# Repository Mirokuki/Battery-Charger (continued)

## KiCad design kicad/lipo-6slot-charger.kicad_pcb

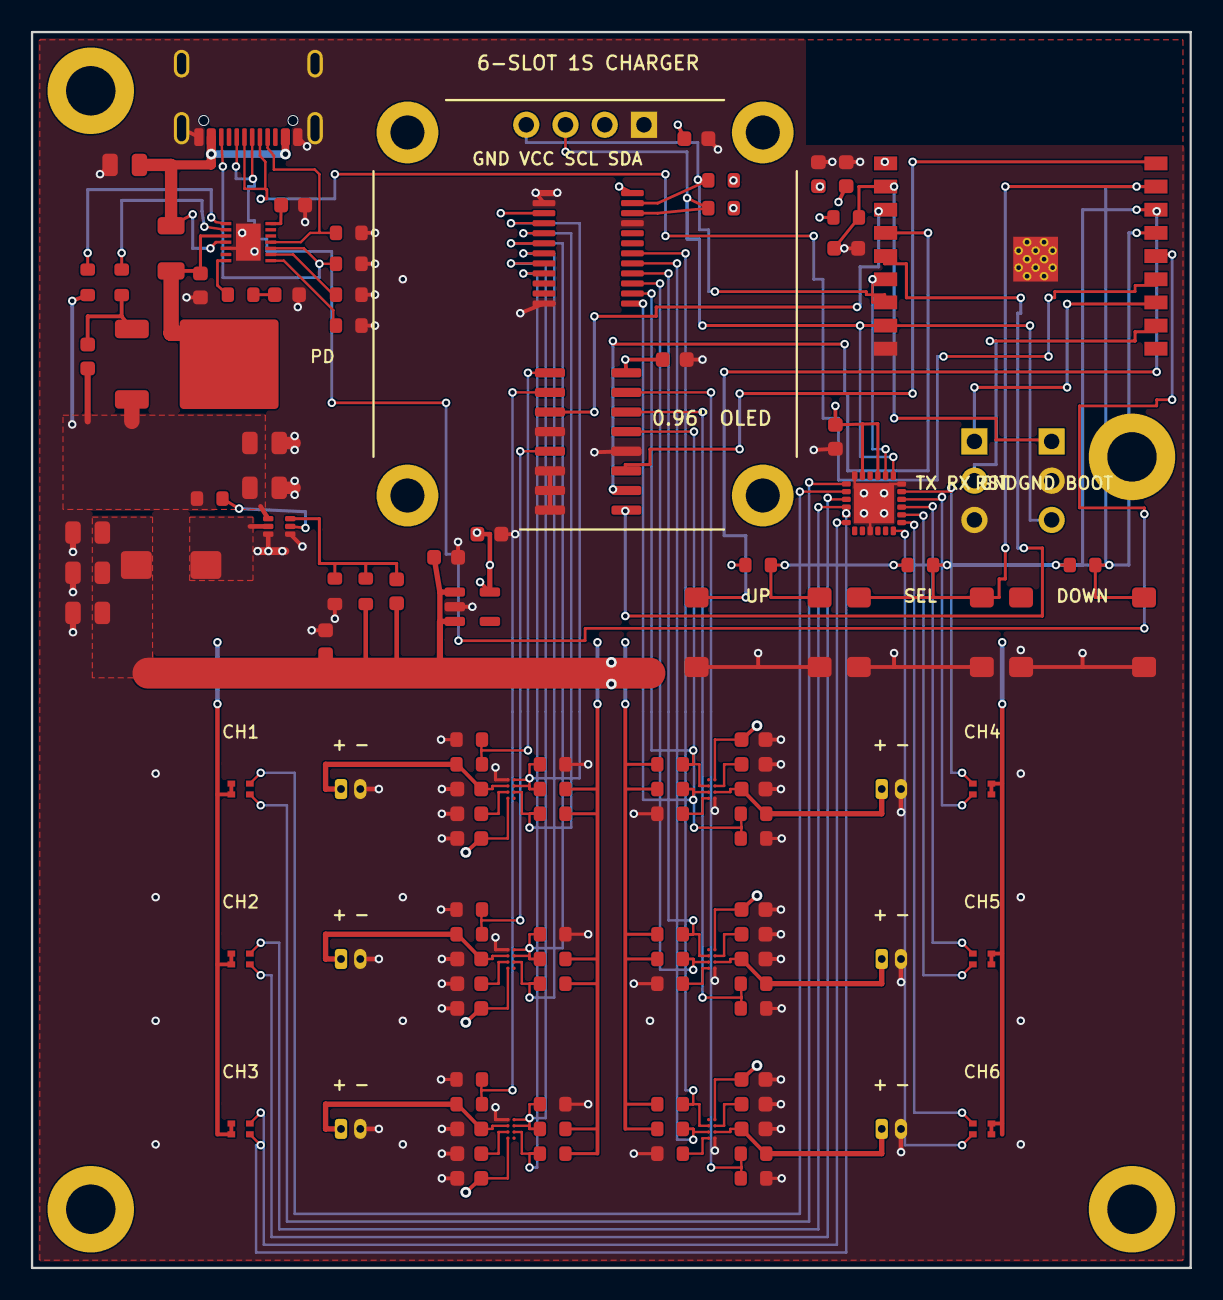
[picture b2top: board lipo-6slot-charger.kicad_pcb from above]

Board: 4 copper layers, 75.0 x 80.0 mm, 127 parts (0 on the bottom side), 81 nets.

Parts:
C1, C2, C8, C10, C101, C102, C103, C104, C105, C106, C201, C202, C203, C204, C205, C206: 1uF_25V; C_0603_1608Metric
C3, C4, C6, C7, C17: 22uF_16V; C_0805_2012Metric
C5: 100pF_25V; C_0603_1608Metric
C9, C13, C301, C302, C303, C304, C305, C306: 10uF_16V; C_0603_1608Metric
C11, C14, C15, C16, C18, C19: 100nF_25V; C_0603_1608Metric
C12: 10uF_25V; C_0805_2012Metric
D1, D2, D3, D4, D5, D6: Dual_0603_Red_Green; LED_LiteOn_LTST-C295K_1.6x0.8mm
D9: PD_STATUS; LED_0603_1608Metric
H1, H2, H3, H4: MountingHole_3.2mm_M3_Pad
H5, H6, H7, H8: MountingHole_2.2mm_M2_Pad
J1: USB4105-GF-A; USB_C_Receptacle_GCT_USB4105-xx-A_16P_TopMnt_Horizontal
J2: OLED_0.96_I2C; PinHeader_1x04_P2.54mm_Vertical
J3: UART; PinHeader_1x03_P2.54mm_Vertical
J4: RST_GND_BOOT; PinHeader_1x03_P2.54mm_Vertical
J101, J102, J103, J104, J105, J106: PicoBlade_1.25mm; Molex_PicoBlade_53047-0210_1x02_P1.25mm_Vertical
L1: 4.7uH_6A; L_Bourns_SRP5030T
Q1: DMN3016LK3; TO-252-2
R1: 82k_1%_9V; R_0603_1608Metric
R2: 100k_1%_Auto; R_0603_1608Metric
R3: 69.8k_1%; R_0603_1608Metric
R4, R101, R102, R103, R104, R105, R106: 10k_1%; R_0603_1608Metric
R5, R6, R9, R10, R18: 10k; R_0603_1608Metric
R7, R8, R401, R402, R403, R404, R405, R406, R501, R502, R503, R504, R505, R506: 4.7k; R_0603_1608Metric
R11, R12, R15: 5.1k_1%; R_0603_1608Metric
R13: 5mR_1%; R_1206_3216Metric
R14: 200R; R_0603_1608Metric
R16: 4.7k_1%; R_0603_1608Metric
R201, R202, R203, R204, R205, R206, R301, R302, R303, R304, R305, R306: 100k_1%; R_0603_1608Metric
SW1: BTN_UP; SW_SPST_PTS645Sx43SMTR92
SW2: BTN_SELECT; SW_SPST_PTS645Sx43SMTR92
SW3: BTN_DOWN; SW_SPST_PTS645Sx43SMTR92
U1: AP33771C; Diodes_W-DFN3030-14_AP33771C
U2: TPS565242DRLR; SOT-563
U3: AP2112K-3.3TRG1; SOT-23-5
U4: ESP32-C3-WROOM-02-N4; ESP32-C3-WROOM-02
U5: TCA9548APWR; TSSOP-24_4.4x7.8mm_P0.65mm
U6: CD74HC4051M96; SOIC-16_3.9x9.9mm_P1.27mm
U7: AW9523BTQR; TQFN-24-1EP_4x4mm_P0.5mm_EP2.6x2.6mm
U101, U102, U103, U104, U105, U106: BQ25188YBGR; TI_DSBGA-8_1.6x1.1mm_P0.4mm_BQ25188

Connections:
/+3V3: C9.1, C13.1, C14.1, C15.1, C16.1, C19.1, D1.3, D1.4, D2.3, D2.4, D3.3, D3.4, D4.3, D4.4, D5.3, D5.4, D6.3, D6.4, J2.2, R6.1, R7.1, R8.1, R9.1, R10.1, R18.1, R401.1, R402.1, R403.1, R404.1, R405.1, R406.1, R501.1, R502.1, R503.1, R504.1, R505.1, R506.1, U3.5, U4.1, U5.3, U5.24, U6.16, U7.21, U7.23
/ADC_MUX_OUT: U4.3, U6.3
/BTN_DOWN: R10.2, SW3.1, U4.15
/BTN_SELECT: R18.2, SW2.1, U4.17
/BTN_UP: R9.2, SW1.1, U4.16
/BUCK_EN: R5.2, U2.5
/BUCK_SW: L1.1, U2.2
/BUCK_VFB: C5.2, R3.2, R4.1, U2.6
/GND: C1.2, C2.2, C3.2, C4.2, C6.2, C7.2, C8.2, C9.2, C10.2, C12.2, C13.2, C14.2, C15.2, C16.2, C17.2, C18.2, C19.2, C101.2, C102.2, C103.2, C104.2, C105.2, C106.2, C201.2, C202.2, C203.2, C204.2, C205.2, C206.2, C301.2, C302.2, C303.2, C304.2, C305.2, C306.2, D9.1, J1.A1, J1.A12, J1.B1, J1.B12, J1.SH, J2.1, J3.3, J4.2, J101.2, J102.2, J103.2, J104.2, J105.2, J106.2, R1.2, R2.2, R4.2, R11.2, R12.2, R101.2, R102.2, R103.2, R104.2, R105.2, R106.2, R301.2, R302.2, R303.2, R304.2, R305.2, R306.2, SW1.2, SW2.2, SW3.2, U1.5, U1.15, U2.3, U2.4, U3.2, U4.9, U4.19, U5.1, U5.2, U5.12, U5.21, U6.4, U6.6, U6.7, U6.8, U6.12, U7.9, U7.18, U7.24, U7.25, U101.D2, U102.D2, U103.D2, U104.D2, U105.D2, U106.D2
/I2C_SCL: J2.3, J4.3, R8.2, U4.8, U5.22, U7.19
/I2C_SDA: J2.4, R7.2, U4.7, U5.23, U7.20
/LED_G_SLOT1: D1.1, U7.1
/LED_G_SLOT2: D2.1, U7.3
/LED_G_SLOT3: D3.1, U7.5
/LED_G_SLOT4: D4.1, U7.17
/LED_G_SLOT5: D5.1, U7.15
/LED_G_SLOT6: D6.1, U7.13
/LED_R_SLOT1: D1.2, U7.2
/LED_R_SLOT2: D2.2, U7.4
/LED_R_SLOT3: D3.2, U7.6
/LED_R_SLOT4: D4.2, U7.16
/LED_R_SLOT5: D5.2, U7.14
/LED_R_SLOT6: D6.2, U7.12
/MCU_EN: C10.1, J4.1, R6.2, U4.2
/MUX_A: U4.18, U6.11
/MUX_B: U4.4, U6.10
/MUX_C: U4.5, U6.9
/PD_GATE: C11.1, Q1.1, R15.2
/PD_ISEL: R2.1, U1.9
/PD_LED: R16.1, U1.7
/PD_LED_A: D9.2, R16.2
/PD_PWR_EN: R15.1, U1.2
/PD_V5V: C2.1, U1.14
/PD_VOUT: R14.2, U1.1
/PD_VSEL: R1.1, U1.8
/SCL_SLOT1: R401.2, U5.5, U101.B1
/SCL_SLOT2: R402.2, U5.7, U102.B1
/SCL_SLOT3: R403.2, U5.9, U103.B1
/SCL_SLOT4: R404.2, U5.14, U104.B1
/SCL_SLOT5: R405.2, U5.16, U105.B1
/SCL_SLOT6: R406.2, U5.18, U106.B1
/SDA_SLOT1: R501.2, U5.4, U101.C1
/SDA_SLOT2: R502.2, U5.6, U102.C1
/SDA_SLOT3: R503.2, U5.8, U103.C1
/SDA_SLOT4: R504.2, U5.13, U104.C1
/SDA_SLOT5: R505.2, U5.15, U105.C1
/SDA_SLOT6: R506.2, U5.17, U106.C1
/Slot_1/TS_NODE: R101.1, U101.D1
/Slot_1/VBAT_SLOT: C201.1, J101.1, R201.1, U101.C2
/Slot_1/VSYS_SLOT: C301.1, U101.B2
/Slot_2/TS_NODE: R102.1, U102.D1
/Slot_2/VBAT_SLOT: C202.1, J102.1, R202.1, U102.C2
/Slot_2/VSYS_SLOT: C302.1, U102.B2
/Slot_3/TS_NODE: R103.1, U103.D1
/Slot_3/VBAT_SLOT: C203.1, J103.1, R203.1, U103.C2
/Slot_3/VSYS_SLOT: C303.1, U103.B2
/Slot_4/TS_NODE: R104.1, U104.D1
/Slot_4/VBAT_SLOT: C204.1, J104.1, R204.1, U104.C2
/Slot_4/VSYS_SLOT: C304.1, U104.B2
/Slot_5/TS_NODE: R105.1, U105.D1
/Slot_5/VBAT_SLOT: C205.1, J105.1, R205.1, U105.C2
/Slot_5/VSYS_SLOT: C305.1, U105.B2
/Slot_6/TS_NODE: R106.1, U106.D1
/Slot_6/VBAT_SLOT: C206.1, J106.1, R206.1, U106.C2
/Slot_6/VSYS_SLOT: C306.1, U106.B2
/UART_RX: J3.2, U4.11
/UART_TX: J3.1, U4.12
/USB_CC1: J1.A5, R11.1, U1.11
/USB_CC2: J1.B5, R12.1, U1.10
/USB_DN: J1.A7, J1.B7, U4.13
/USB_DP: J1.A6, J1.B6, U4.14
/VBUS_9V: C3.1, C4.1, C11.2, Q1.3, R5.1, R14.1, U2.1
/VBUS_RAW: C12.1, J1.A4, J1.A9, J1.B4, J1.B9, R13.1, U1.4
/VBUS_SNS: C1.1, Q1.2, R13.2, U1.3
/VIN_4V8: C5.1, C6.1, C7.1, C8.1, C17.1, C18.1, C101.1, C102.1, C103.1, C104.1, C105.1, C106.1, L1.2, R3.1, U3.1, U3.3, U101.A2, U102.A2, U103.A2, U104.A2, U105.A2, U106.A2
/VSENSE_SLOT1: R201.2, R301.1, U6.1
/VSENSE_SLOT2: R202.2, R302.1, U6.5
/VSENSE_SLOT3: R203.2, R303.1, U6.2
/VSENSE_SLOT4: R204.2, R304.1, U6.13
/VSENSE_SLOT5: R205.2, R305.1, U6.14
/VSENSE_SLOT6: R206.2, R306.1, U6.15

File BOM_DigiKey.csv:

DigiKey Part Number,Quantity,Reference Designator,Manufacturer Part Number,Manufacturer,Description,Unit Price (USD),Line Total (USD),DigiKey Link,Notes
2073-USB4105-GF-A-120CT-ND,1,J1,USB4105-GF-A-120,GCT,USB-C Receptacle 16P,0.78,0.78,https://www.digikey.com/en/products/detail/gct/USB4105-GF-A-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,USB 2.0 Type-C receptacle with 1.20mm shell stakes (fits standard 1.6mm PCB)
31-AP33771CFBZ-13-FA02CT-ND,1,U1,AP33771CFBZ-13-FA02,Diodes Inc.,USB PD 3.1 Sink Controller,1.45,1.45,https://www.digikey.com/en/products/detail/diodes-incorporat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,USB PD 3.1 Sink Controller (requests 9V @ Auto up to 3A)
DMN3016LK3-13DICT-ND,1,Q1,DMN3016LK3-13,Diodes Inc.,30V 12.4A N-MOSFET,0.58,0.58,https://www.digikey.com/en/products/detail/diodes-incorporat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,TO-252-3 N-Channel MOSFET for VBUS power path switch
296-TPS565242DRLRCT-ND,1,U2,TPS565242DRLR,Texas Instruments,5A Synchronous Buck Converter,1.20,1.20,https://www.digikey.com/en/products/detail/texas-instruments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,SOT-563 3V-16V to 4.80V 5A synchronous buck
SRP5030T-4R7MCT-ND,1,L1,SRP5030T-4R7M,Bourns,4.7uH 4.6A Power Inductor,0.68,0.68,https://www.digikey.com/en/products/detail/bourns-inc/SRP503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,4.7uH Shielded Drum Core Inductor 4.6A Irms / 6A Isat
AP2112K-3.3TRG1DICT-ND,1,U3,AP2112K-3.3TRG1,Diodes Inc.,3.3V 600mA LDO Regulator,0.43,0.43,https://www.digikey.com/en/products/detail/diodes-incorporat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,SOT-25 Ultra-low dropout 3.3V regulator for ESP32 & I2C
1965-ESP32-C3-WROOM-02-N4CT-ND,1,U4,ESP32-C3-WROOM-02-N4,Espressif Systems,ESP32-C3 RISC-V Module,3.38,3.38,https://www.digikey.com/en/products/detail/espressif-systems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,BLE 5.0 + Wi-Fi module with PCB antenna and 4MB flash
296-34905-1-ND,1,U5,TCA9548APWR,Texas Instruments,8-Channel I2C Multiplexer,1.69,1.69,https://www.digikey.com/en/products/detail/texas-instruments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,TSSOP-24 8-ch I2C switch (channels 0-5 for 6x BQ25188)
296-14530-1-ND,1,U6,CD74HC4051M96,Texas Instruments,8-Channel Analog MUX,0.52,0.52,https://www.digikey.com/en/products/detail/texas-instruments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,SOIC-16 Analog Multiplexer for ADC battery sense
1528-AW9523-ND,1,U7,AW9523BTQR,Awinic,16-Ch I2C LED Driver,0.32,0.32,https://www.digikey.com/en/products/detail/adafruit-industri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,TQFN-24 16-channel constant-current LED driver & GPIO expander (I2C addr 0x5B)
296-BQ25188YBGRCT-ND,6,U101-U106,BQ25188YBGR,Texas Instruments,1S 1A I2C LiPo Charger,1.35,8.10,https://www.digikey.com/en/products/detail/texas-instruments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,DSBGA-8 1A I2C Linear Charger (4.20V LiPo / 4.35V LiHV)
WM1731-ND,6,J101-J106,0530470210,Molex,PicoBlade 1.25mm 2-Pin,0.22,1.32,https://www.digikey.com/en/products/detail/molex/0530470210/240562,Molex PicoBlade 1.25mm 2-circuit vertical header
160-1828-1-ND,6,D1-D6,LTST-C295KGKRKT,Lite-On Inc.,Dual Red/Green 0603 LED,0.18,1.08,https://www.digikey.com/en/products/detail/lite-on-inc/LTST-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,"0603 SMD Bi-Color LED (Common Anode 3.3V, Pin 1=Green K, Pin 2=Red K)"
160-LTST-C190GKTCT-ND,1,D9,LTST-C190GKT,Lite-On Inc.,0603 Green LED,0.12,0.12,https://www.digikey.com/en/products/detail/lite-on-inc/LTST-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,0603 Green LED for AP33771C PD Status indicator
609-3252-ND,1,J2-J4,68000-140HLF,Amphenol ICC,40-Pin 2.54mm Breakaway Header,0.48,0.48,https://www.digikey.com/en/products/detail/amphenol-cs-fci/6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,"40-Pin 2.54mm breakaway strip (snaps into 1x4 for OLED, 1x3 for UART, 1x3 for BOOT)"
CKN9112CT-ND,3,SW1-SW3,PTS645SM43SMTR92 LFS,C&K / Littelfuse,6mm SMD Tactile Switch,0.28,0.84,https://www.digikey.com/en/products/detail/c-k/PTS645SM43SMT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,"6x6mm SMT Tactile Switch 4.3mm actuator height (UP, SELECT, DOWN)"
13-PE1206FKF470R005ZCT-ND,1,R13,PE1206FKF470R005Z,YAGEO,5mR 1% 1W Current Sense,0.35,0.35,https://www.digikey.com/en/products/detail/yageo/PE1206FKF47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,1206 5 mOhm 1% 1W Metal Foil Current Sense Resistor (AP33771C ISENSE)
587-2980-1-ND,5,"C3-C4, C6-C7, C17",EMK212BBJ226MG-T,Taiyo Yuden,22uF 16V 0805 X5R,0.16,0.80,https://www.digikey.com/en/products/detail/taiyo-yuden/EMK21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,Consolidated 0805 bulk capacitors: Buck in (9V) and Buck out (4.80V)
13-CC0805KKX6S8BB106CT-ND,1,C12,CC0805KKX6S8BB106,YAGEO,10uF 25V 0805 X6S,0.12,0.12,https://www.digikey.com/en/products/detail/yageo/CC0805KKX6S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,AP33771C VBUS input bypass. Must stay <=10uF (USB-C sink VBUS capacitance limit at attach); 25V for margin on exposed connector
311-1822-1-ND,8,"C9, C13, C301-C306",CC0603MRX5R7BB106,YAGEO,10uF 16V 0603 X5R,0.08,0.64,https://www.digikey.com/en/products/detail/yageo/CC0603MRX5R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,"0603 10uF 16V LDO output, ESP32 bypass, and BQ25188 SYS capacitors"
311-1802-1-ND,16,"C1-C2, C8, C10, C101-C106, C201-C206",CC0603KRX7R8BB105,YAGEO,1uF 25V 0603 X7R,0.04,0.64,https://www.digikey.com/en/products/detail/yageo/CC0603KRX7R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,Consolidated 0603 1uF 25V X7R decoupling for all 6 BQ25188 IN & BAT pins + logic (10+ price break)
311-1341-1-ND,6,"C11, C14-C16, C18-C19",CC0603KRX7R8BB104,YAGEO,100nF 25V 0603 X7R,0.03,0.18,https://www.digikey.com/en/products/detail/yageo/CC0603KRX7R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,Consolidated 100nF 25V 0603 bypass capacitors + AP33771C MOSFET gate slew capacitor
311-1069-1-ND,1,C5,CC0603JRNPO9BN101,YAGEO,100pF 50V 0603 C0G,0.03,0.03,https://www.digikey.com/en/products/detail/yageo/CC0603JRNPO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,TPS565242 Buck feedforward capacitor
311-82.0KHRCT-ND,1,R1,RC0603FR-0782KL,YAGEO,82k 1% 0603,0.03,0.03,https://www.digikey.com/en/products/detail/yageo/RC0603FR-07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,AP33771C VSEL = 82k (Sets PD target voltage = 9V)
311-100KHRCT-ND,13,"R2, R201-R206, R301-R306",RC0603FR-07100KL,YAGEO,100k 1% 0603,0.03,0.39,https://www.digikey.com/en/products/detail/yageo/RC0603FR-07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,R2: AP33771C ISEL=100k (Auto negotiate up to 3A); R201-R306: ADC 2:1 battery dividers
311-69.8KHRCT-ND,1,R3,RC0603FR-0769K8L,YAGEO,69.8k 1% 0603,0.03,0.03,https://www.digikey.com/en/products/detail/yageo/RC0603FR-07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,TPS565242 Top FB resistor (VOUT = 0.6V * (1 + 69.8k/10k) = 4.788V)
311-5.10KHRCT-ND,3,"R11-R12, R15",RC0603FR-075K1L,YAGEO,5.1k 1% 0603,0.03,0.09,https://www.digikey.com/en/products/detail/yageo/RC0603FR-07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,5.1k 1% 0603: USB-C CC1/CC2 pull-downs + AP33771C MOSFET gate drive
311-200HRCT-ND,1,R14,RC0603FR-07200RL,YAGEO,200R 1% 0603,0.03,0.03,https://www.digikey.com/en/products/detail/yageo/RC0603FR-07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,AP33771C VOUT sense monitor series resistor
311-10.0KHRCT-ND,12,"R4-R6, R9-R10, R18, R101-R106",RC0603FR-0710KL,YAGEO,10k 1% 0603,0.03,0.36,https://www.digikey.com/en/products/detail/yageo/RC0603FR-07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,"10k 1% 0603: Buck Bot FB (R4), Buttons, I2C reset lines, and 6x BQ25188 TS pull-downs"
311-4.70KHRCT-ND,15,"R7-R8, R16, R401-R406, R501-R506",RC0603FR-074K7L,YAGEO,4.7k 1% 0603,0.03,0.45,https://www.digikey.com/en/products/detail/yageo/RC0603FR-07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,4.7k 1% 0603: I2C bus pull-ups (main bus & 6x isolated slots) + PD LED indicator
,,,,,"ESTIMATED TOTAL (qty 1, before cut-tape fees)",,27.11,,

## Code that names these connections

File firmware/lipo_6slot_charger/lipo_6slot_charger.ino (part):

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#include <freertos/semphr.h>

// --- Pin Definitions (Matches KiCad Schematic) ---
#define PIN_MUX_A        0   // GPIO0 -> CD74HC4051 S0 (Pin 11)
#define PIN_BTN_SELECT   1   // GPIO1 <- SW2 (SELECT)
#define PIN_BTN_UP       2   // GPIO2 <- SW1 (UP)
#define PIN_BTN_DOWN     3   // GPIO3 <- SW3 (DOWN)
#define PIN_ADC_MUX_OUT  4   // GPIO4 (ADC1_CH4) <- CD74HC4051 COM (Pin 3)
#define PIN_MUX_B        5   // GPIO5 -> CD74HC4051 S1 (Pin 10)
#define PIN_MUX_C        6   // GPIO6 -> CD74HC4051 S2 (Pin 9)
// GPIO7 is now No Connect (U7 level shifter removed, AW9523B is on I2C)
#define PIN_I2C_SDA      8   // GPIO8 -> Master I2C SDA (TCA9548A + OLED)
#define PIN_I2C_SCL      9   // GPIO9 -> Master I2C SCL (TCA9548A + OLED), J4 Pin 3 (BOOT jumper)

// --- I2C Addresses ---
#define TCA9548A_ADDR    0x70
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uint16_t readSlotVoltage_mV(uint8_t slot) {
  if (slot >= NUM_SLOTS) return 0;
  uint8_t channel = ADC_MUX_CHANNEL[slot];
  digitalWrite(PIN_MUX_A, (channel & 0x01) ? HIGH : LOW);
  digitalWrite(PIN_MUX_B, (channel & 0x02) ? HIGH : LOW);
  digitalWrite(PIN_MUX_C, (channel & 0x04) ? HIGH : LOW);
  delayMicroseconds(200);

  uint32_t samples[16];
  for (int i = 0; i < 16; i++) {
    samples[i] = analogReadMilliVolts(PIN_ADC_MUX_OUT);
    delayMicroseconds(20);
  }
  // Simple insertion sort to pick median
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  if (millis() - lastBtnCheck < 150) return;
  lastBtnCheck = millis();

  bool btnUp = (digitalRead(PIN_BTN_UP) == LOW);
  bool btnSel = (digitalRead(PIN_BTN_SELECT) == LOW);
  bool btnDown = (digitalRead(PIN_BTN_DOWN) == LOW);

  if (btnUp) {
    LockGuard lock;
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  Serial.begin(115200);
  stateMutex = xSemaphoreCreateMutex();

  pinMode(PIN_MUX_A, OUTPUT);
  pinMode(PIN_MUX_B, OUTPUT);
  pinMode(PIN_MUX_C, OUTPUT);
  pinMode(PIN_BTN_SELECT, INPUT_PULLUP);
  pinMode(PIN_BTN_UP, INPUT_PULLUP);
  pinMode(PIN_BTN_DOWN, INPUT_PULLUP);

  analogReadResolution(12);
  analogSetPinAttenuation(PIN_ADC_MUX_OUT, ADC_11db);

  Wire.begin(PIN_I2C_SDA, PIN_I2C_SCL, 400000);
  deselectI2CMux();

  // Initialize GeeekPi 0.96" SSD1306 OLED
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
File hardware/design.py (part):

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      12: None, 13: None, 14: "PD_V5V", 15: GND},
     "AP33771CFBZ-13-FA02", "")
NC_PINS.discard(("U1", "1"))
PARTS["U1"]["pins"]["1"] = "PD_VOUT"
part("R3", "Device:R", "Resistor_SMD:R_1206_3216Metric", "5mR 1%",
     {1: "VBUS_RAW", 2: "VBUS_SNS"}, "PE1206FKF470R005Z", "")
part("Q1", "Transistor_FET:AO3400A", SOT23, "AO3400A",
     {1: "PD_GATE", 2: VBUS, 3: "VBUS_SNS"}, "AO3400A", "C20917")
R("R4", "6.2k", "PD_PWR_EN", "PD_GATE")
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R("R17", "100k", "BUZZ", GND)

# ---------------------------------------------------------------- I2C mux
mux_pins = {1: GND, 2: GND, 21: GND, 3: "MUX_RST_N", 12: GND, 24: V33, 22: "I2C_SCL", 23: "I2C_SDA",
            17: None, 18: None, 19: None, 20: None}
for s in range(1, SLOTS + 1):
    mux_pins[4 + 2 * (s - 1) if s <= 4 else 13 + 2 * (s - 5)] = f"S{s}_SDA"
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
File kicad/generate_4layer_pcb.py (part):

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    pos["U4"] = (64.0, 14.5, 0.0)
    pos["C14"] = (52.7, 9.2, 90.0)
    pos["C13"] = (50.9, 9.2, 90.0)
    # R6 and C10 directly beside U4 pin 2 (MCU_EN at 55.25, 10.0)
    pos["R6"] = (52.7, 12.0, 0.0)
    pos["C10"] = (52.7, 14.0, 0.0)
    pos["U7"] = (54.5, 30.5, 0.0)
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    # Start at 7.5 to overlap with F.Cu buck zone and eliminate dangling left tail
    cu.track("/VIN_4V8", [(7.5, TRUNK_Y), (40.0, TRUNK_Y)], 2.0)
    for vy in (40.8, 42.2):
        cu.via("/VIN_4V8", SPINE_X, vy, POWER_VIA_D, POWER_VIA_DRILL)

    # U3 SOT-25 LDO cleanly routed (no shorts through Pin 2 GND!)
    u3_1 = pad("U3", "1")
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    c9_1 = pad("C9", "1")
    c9_2 = pad("C9", "2")

    # VIN_4V8: Route Pin 1 and Pin 3 west around Pin 2, connect to C8.1 and TRUNK_Y
    cu.track("/VIN_4V8", [u3_3, (26.4, u3_3[1]), (26.4, u3_1[1]), u3_1], 0.35)
    cu.track("/VIN_4V8", [(26.4, u3_1[1]), c8_1], 0.35)
    cu.track("/VIN_4V8", [(26.4, u3_3[1]), (26.4, TRUNK_Y)], 0.40)
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    sda_pin, scl_pin = cu.pad("J2", "4"), cu.pad("J2", "3")
    sda_x, sda_y = I2C_DROP["/I2C_SDA"]
    scl_x, scl_y = I2C_DROP["/I2C_SCL"]
    cu.track("/I2C_SDA", [sda_pin, (sda_pin[0], 7.15), (sda_x, 7.15), (sda_x, sda_y)], 0.18, pcbnew.B_Cu)
    cu.via("/I2C_SDA", sda_x, sda_y)
    cu.track("/I2C_SCL", [scl_pin, (scl_pin[0], 7.75)], 0.18)
    cu.via("/I2C_SCL", scl_pin[0], 7.75)
    cu.track("/I2C_SCL", [(scl_pin[0], 7.75), (scl_x, 7.75), (scl_x, scl_y)], 0.18, pcbnew.B_Cu)
    cu.via("/I2C_SCL", scl_x, scl_y)
    cu.track("/I2C_SDA", [(sda_x, sda_y), cu.pad("R7", "2")], 0.18)
    cu.track("/I2C_SCL", [(scl_x, scl_y), cu.pad("R8", "2")], 0.18)
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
